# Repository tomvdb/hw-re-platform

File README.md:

Hardware Reverse Engineering Learning Platform
==============================================

Current Status:

2014/07/17: Boards received, concept works, pcb has some minor issues. Working on v2
2014/06/20: PCB's sent for manufacturing - Not Tested Yet

I enjoy trying to reverse engineer the famous crackme and reverseme executables in my spare time. After reading the xbox reverse engineering book by bunnie I went looking at the my options for learning and experimenting with hardware reverse engineering. Unfortunately the options are few and expensive.

The hardware reverse engineering platform is basically a shield for the new stm32 nucleo boards using the st-morpho connectors. It contains two arduino compatible microcontrollers and an eeprom. There are 8 data lines connected between the two microcontrollers and there is also i2c lines connecting the mcu's with an eeprom. The nucleo board handles loading the reverse engineering scenario on the shield (firmware on the avr's and data on the eeprom). Test pins are added on all the data lines for connection to RE tools. This allows anyone to easily create firmware that depicts a possible RE situation. For example the two mcu's can communicate with each other using a certain protocol.

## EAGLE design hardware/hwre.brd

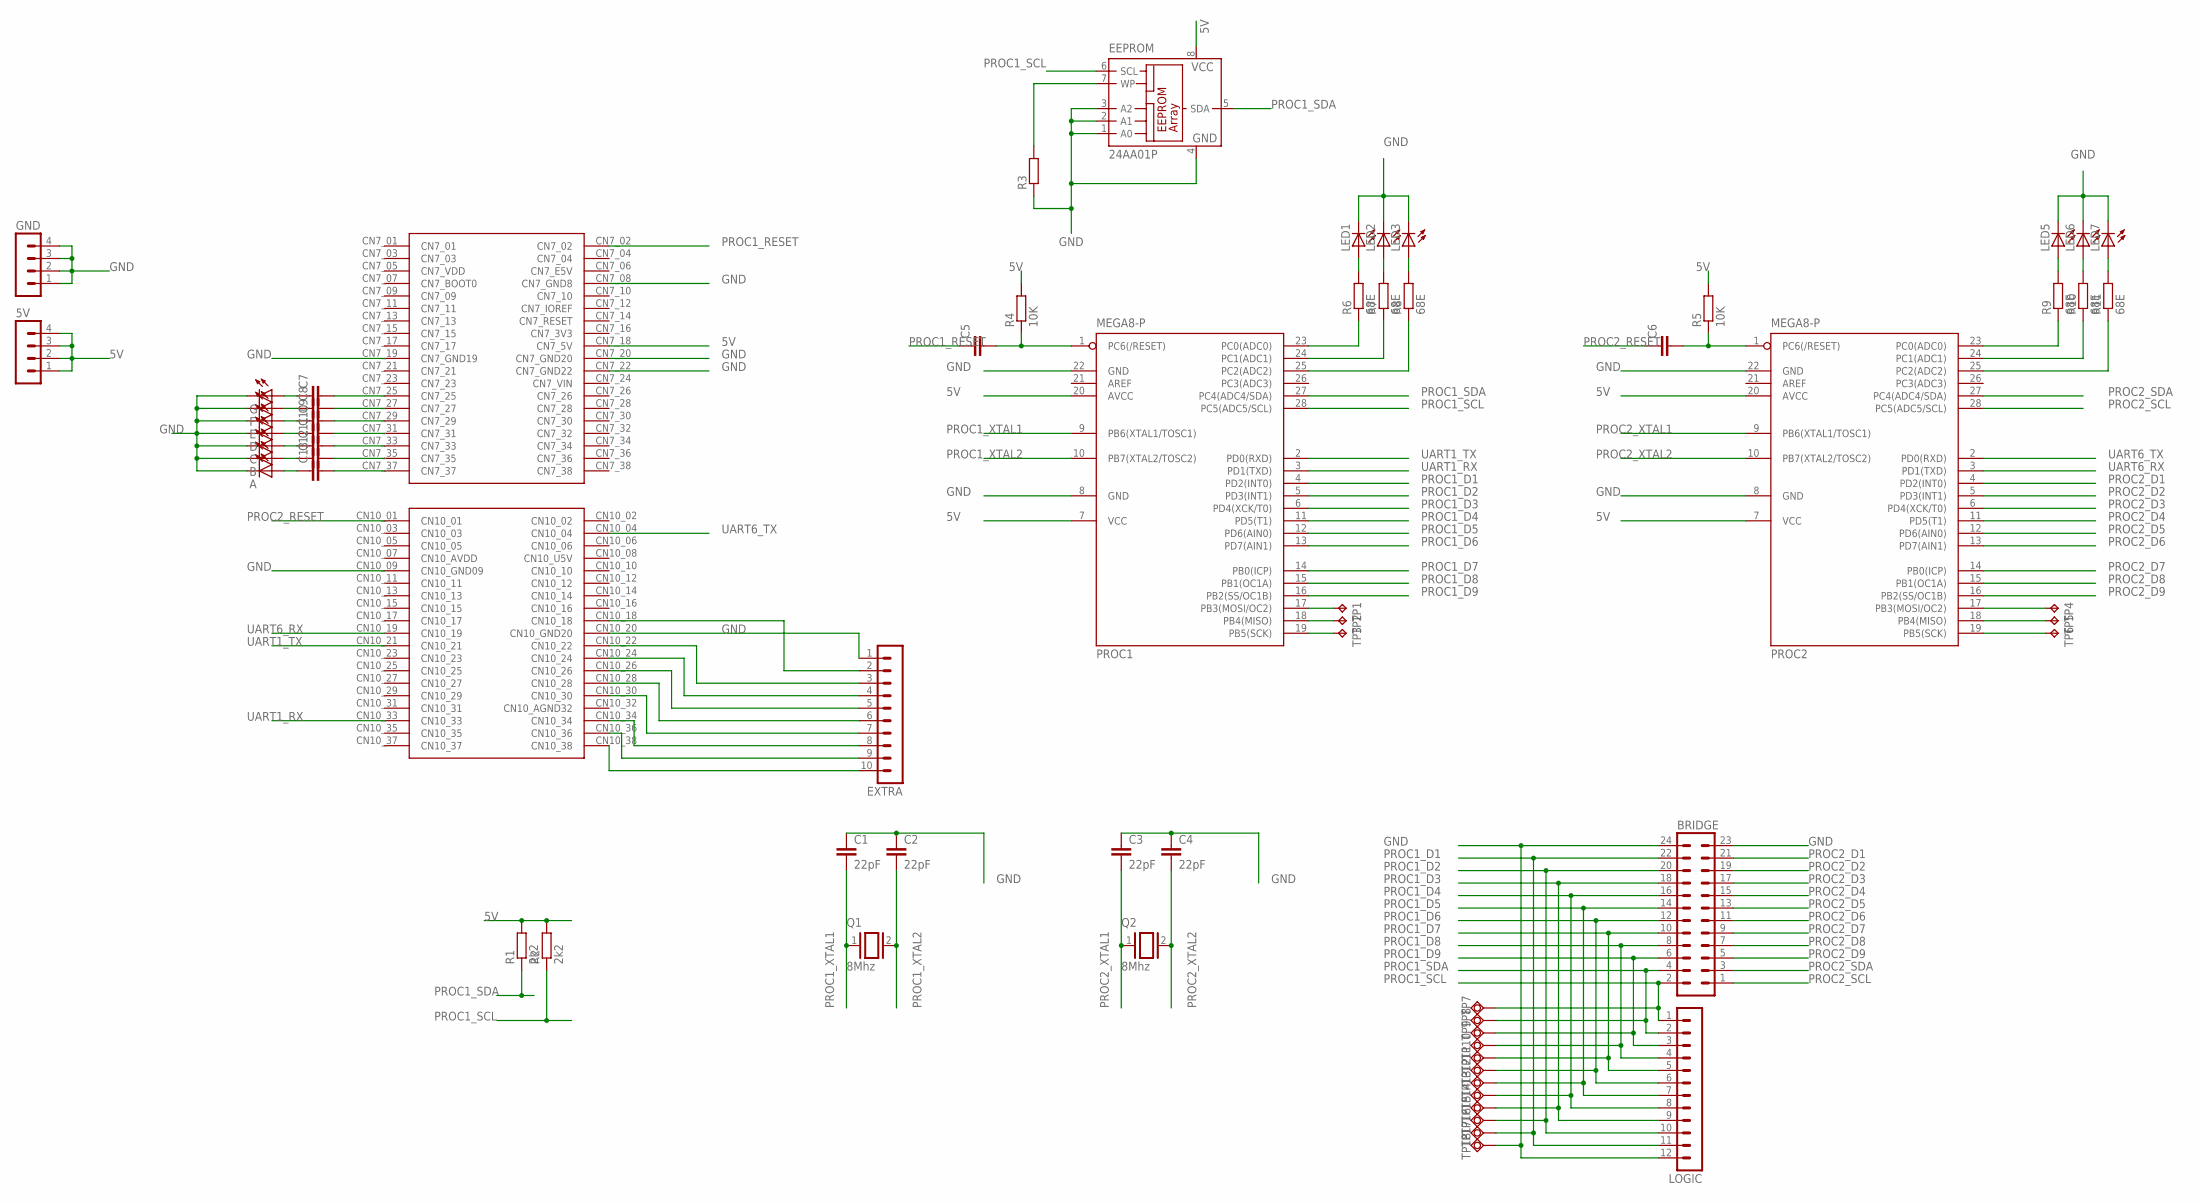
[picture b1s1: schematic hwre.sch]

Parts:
5V: MA04-1
A: LEDCHIP-LED0603; CHIP-LED0603
B: LEDCHIP-LED0603; CHIP-LED0603
BRIDGE: MA12-2
C: LEDCHIP-LED0603; CHIP-LED0603
C1, C2, C3, C4: 22pF; C0603
C5, C6, C7, C8, C9, C10, C11, C12, C13: C-EUC0603; C0603
D: LEDCHIP-LED0603; CHIP-LED0603
E: LEDCHIP-LED0603; CHIP-LED0603
EEPROM: 24AA01P; DIL8
EXTRA: MA10-1
F: LEDCHIP-LED0603; CHIP-LED0603
G: LEDCHIP-LED0603; CHIP-LED0603
GND: MA04-1
LED1, LED2, LED3, LED5, LED6, LED7: LEDSML0805; SML0805
LOGIC: MA12-1
PROC1, PROC2: MEGA8-P; DIL28-3
Q1, Q2: 8Mhz; QS
R1, R2: 2k2; R0603
R3: R-EU_R0603; R0603
R4, R5: 10K; R0603
R6, R7, R8, R9, R10, R11: 68E; R0603
TP1, TP2, TP3, TP4, TP5, TP6: TPTP20R; TP20R
TP7, TP8, TP9, TP10, TP11, TP12, TP13, TP14, TP15, TP16, TP17, TP18: TPSQTP20R; TP20R
U$1: NUCLEO_SHIELDGENERIC; NUCLEO_SHIELD

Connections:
5V: 5V.1, 5V.2, 5V.3, 5V.4, EEPROM.8 (VCC), PROC1.7 (VCC), PROC1.20 (AVCC), PROC2.7 (VCC), PROC2.20 (AVCC), R1.2, R2.2, R4.2, R5.2, U$1.CN7_18 (CN7_5V)
GND: A.C, B.C, BRIDGE.23, BRIDGE.24, C.C, C1.1, C2.1, C3.1, C4.1, D.C, E.C, EEPROM.1 (A0), EEPROM.2 (A1), EEPROM.3 (A2), EEPROM.4 (GND), EXTRA.1, F.C, G.C, GND.1, GND.2, GND.3, GND.4, LED1.C, LED2.C, LED3.C, LED5.C, LED6.C, LED7.C, LOGIC.12, PROC1.8 (GND), PROC1.22 (GND), PROC2.8 (GND), PROC2.22 (GND), R3.1, TP18.TP, U$1.CN7_08 (CN7_GND8), U$1.CN7_19 (CN7_GND19), U$1.CN7_20 (CN7_GND20), U$1.CN7_22 (CN7_GND22), U$1.CN10_09 (CN10_GND09), U$1.CN10_20 (CN10_GND20)
unnamed: PROC1.23 (PC0(ADC0)), R6.1
unnamed: PROC1.24 (PC1(ADC1)), R7.1
unnamed: PROC1.25 (PC2(ADC2)), R8.1
unnamed: LED1.A, R6.2
unnamed: LED2.A, R7.2
unnamed: EEPROM.7 (WP), R3.2
unnamed: LED3.A, R8.2
unnamed: PROC1.17 (PB3(MOSI/OC2)), TP1.TP
unnamed: PROC2.23 (PC0(ADC0)), R9.1
unnamed: PROC2.24 (PC1(ADC1)), R10.1
unnamed: PROC2.25 (PC2(ADC2)), R11.1
unnamed: LED5.A, R9.2
unnamed: LED6.A, R10.2
unnamed: LED7.A, R11.2
unnamed: PROC1.18 (PB4(MISO)), TP2.TP
unnamed: PROC1.19 (PB5(SCK)), TP3.TP
unnamed: PROC2.17 (PB3(MOSI/OC2)), TP4.TP
unnamed: PROC2.18 (PB4(MISO)), TP5.TP
unnamed: PROC2.19 (PB5(SCK)), TP6.TP
unnamed: C7.2, U$1.CN7_25
unnamed: C8.2, U$1.CN7_27
unnamed: C9.2, U$1.CN7_29
unnamed: C10.2, U$1.CN7_31
unnamed: C11.2, U$1.CN7_33
unnamed: C12.2, U$1.CN7_35
unnamed: C13.2, U$1.CN7_37
unnamed: C7.1, G.A
unnamed: C8.1, F.A
unnamed: C9.1, E.A
unnamed: C10.1, D.A
unnamed: C.A, C11.1
unnamed: B.A, C12.1
unnamed: A.A, C13.1
unnamed: EXTRA.10, U$1.CN10_38
unnamed: EXTRA.9, U$1.CN10_36
unnamed: EXTRA.8, U$1.CN10_34
unnamed: EXTRA.7, U$1.CN10_30
unnamed: EXTRA.6, U$1.CN10_28
unnamed: EXTRA.5, U$1.CN10_26
unnamed: EXTRA.4, U$1.CN10_24
unnamed: EXTRA.3, U$1.CN10_22
unnamed: EXTRA.2, U$1.CN10_18
PC6: C5.2, PROC1.1 (PC6(/RESET)), R4.1
PROC1_D1: BRIDGE.22, LOGIC.11, PROC1.4 (PD2(INT0)), TP17.TP
PROC1_D2: BRIDGE.20, LOGIC.10, PROC1.5 (PD3(INT1)), TP16.TP
PROC1_D3: BRIDGE.18, LOGIC.9, PROC1.6 (PD4(XCK/T0)), TP15.TP
PROC1_D4: BRIDGE.16, LOGIC.8, PROC1.11 (PD5(T1)), TP14.TP
PROC1_D5: BRIDGE.14, LOGIC.7, PROC1.12 (PD6(AIN0)), TP13.TP
PROC1_D6: BRIDGE.12, LOGIC.6, PROC1.13 (PD7(AIN1)), TP12.TP
PROC1_D7: BRIDGE.10, LOGIC.5, PROC1.14 (PB0(ICP)), TP11.TP
PROC1_D8: BRIDGE.8, LOGIC.4, PROC1.15 (PB1(OC1A)), TP10.TP
PROC1_D9: BRIDGE.6, LOGIC.3, PROC1.16 (PB2(SS/OC1B)), TP9.TP
PROC1_RESET: C5.1, U$1.CN7_02
PROC1_SCL: BRIDGE.2, EEPROM.6 (SCL), LOGIC.1, PROC1.28 (PC5(ADC5/SCL)), R2.1, TP7.TP
PROC1_SDA: BRIDGE.4, EEPROM.5 (SDA), LOGIC.2, PROC1.27 (PC4(ADC4/SDA)), R1.1, TP8.TP
PROC1_XTAL1: C1.2, PROC1.9 (PB6(XTAL1/TOSC1)), Q1.1
PROC1_XTAL2: C2.2, PROC1.10 (PB7(XTAL2/TOSC2)), Q1.2
PROC2_D1: BRIDGE.21, PROC2.4 (PD2(INT0))
PROC2_D2: BRIDGE.19, PROC2.5 (PD3(INT1))
PROC2_D3: BRIDGE.17, PROC2.6 (PD4(XCK/T0))
PROC2_D4: BRIDGE.15, PROC2.11 (PD5(T1))
PROC2_D5: BRIDGE.13, PROC2.12 (PD6(AIN0))
PROC2_D6: BRIDGE.11, PROC2.13 (PD7(AIN1))
PROC2_D7: BRIDGE.9, PROC2.14 (PB0(ICP))
PROC2_D8: BRIDGE.7, PROC2.15 (PB1(OC1A))
PROC2_D9: BRIDGE.5, PROC2.16 (PB2(SS/OC1B))
PROC2_PC6: C6.2, PROC2.1 (PC6(/RESET)), R5.1
PROC2_RESET: C6.1, U$1.CN10_01
PROC2_SCL: BRIDGE.1, PROC2.28 (PC5(ADC5/SCL))
PROC2_SDA: BRIDGE.3, PROC2.27 (PC4(ADC4/SDA))
PROC2_XTAL1: C3.2, PROC2.9 (PB6(XTAL1/TOSC1)), Q2.1
PROC2_XTAL2: C4.2, PROC2.10 (PB7(XTAL2/TOSC2)), Q2.2
UART1_RX: PROC1.3 (PD1(TXD)), U$1.CN10_33
UART1_TX: PROC1.2 (PD0(RXD)), U$1.CN10_21
UART6_RX: PROC2.3 (PD1(TXD)), U$1.CN10_19
UART6_TX: PROC2.2 (PD0(RXD)), U$1.CN10_04

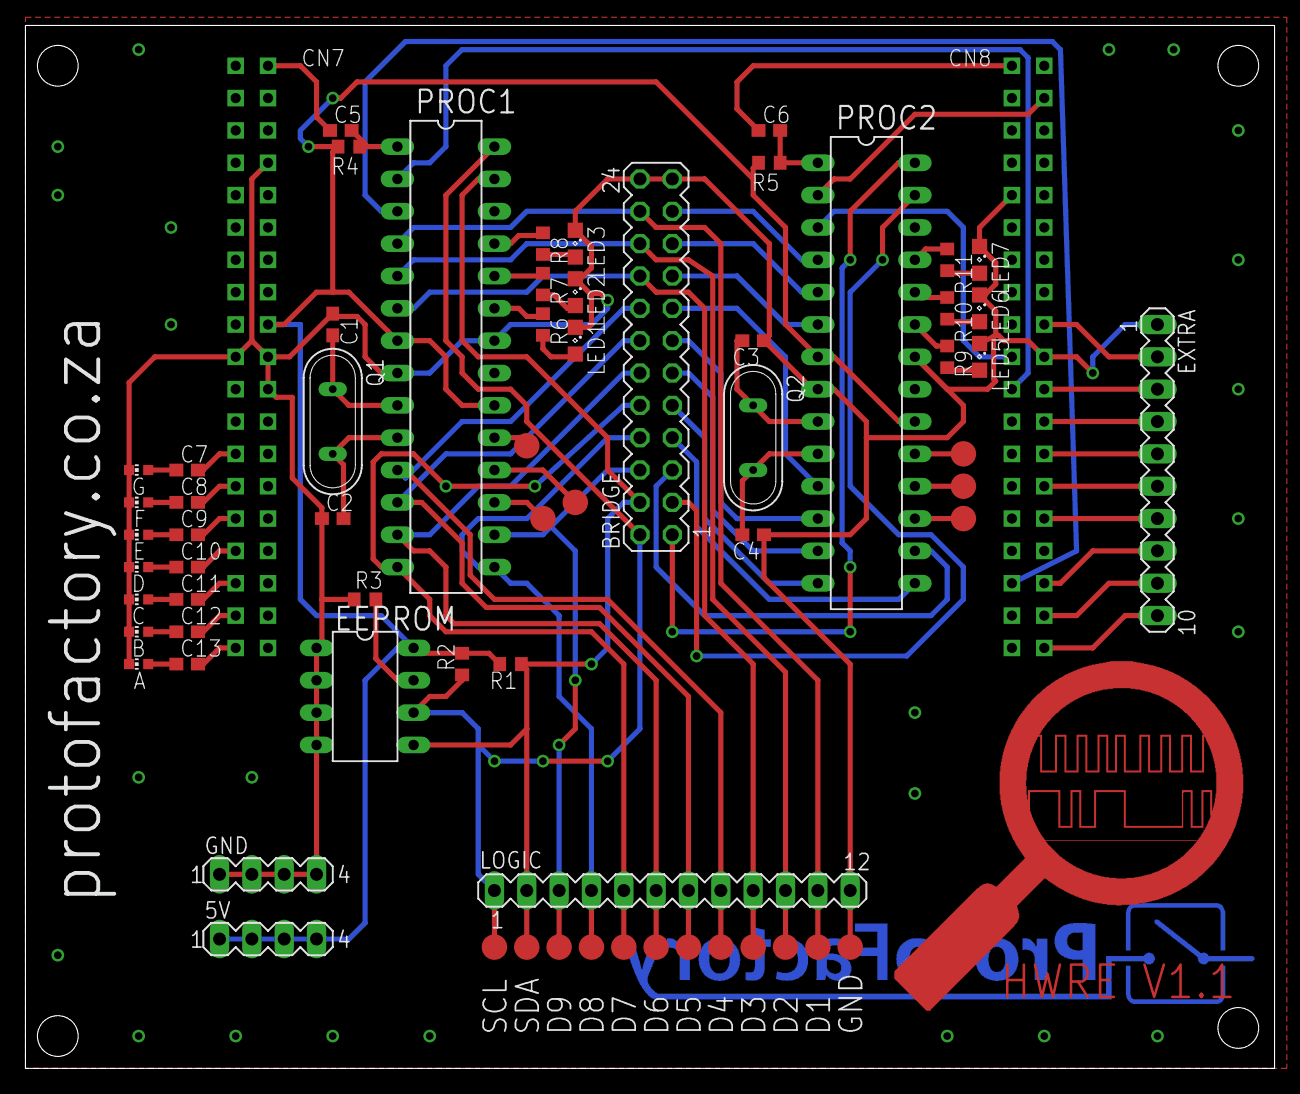
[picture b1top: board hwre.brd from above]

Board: 2 copper layers, 98.1 x 81.9 mm, 68 parts (1 on the bottom side), 78 nets.

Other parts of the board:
U$2: HWRE
U$3: LOGO

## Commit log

2014-07-14 added logo and some doc pics
2014-07-22 updated pcb to hwre v1.1
